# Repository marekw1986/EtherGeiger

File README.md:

# EtherGeiger

## Overview

This is firmware for Ethergeiger project, described on my [Hackaday.io profile](https://hackaday.io/project/163717-ethergeiger-20).

## Required Tools

Project was created in Microchip MPLAB X IDE.
It uses legacy plib.h (https://www.microchip.com/SWLibraryWeb/product.aspx?product=PIC32%20Peripheral%20Library) and MLA libraries (https://www.microchip.com/en-us/tools-resources/develop/libraries/microchip-libraries-for-applications).
You need to use older version of XC32 compiler to build this project (tested with v2.40). Attempt to build it with never version (like 4.xx) leads linker issues.

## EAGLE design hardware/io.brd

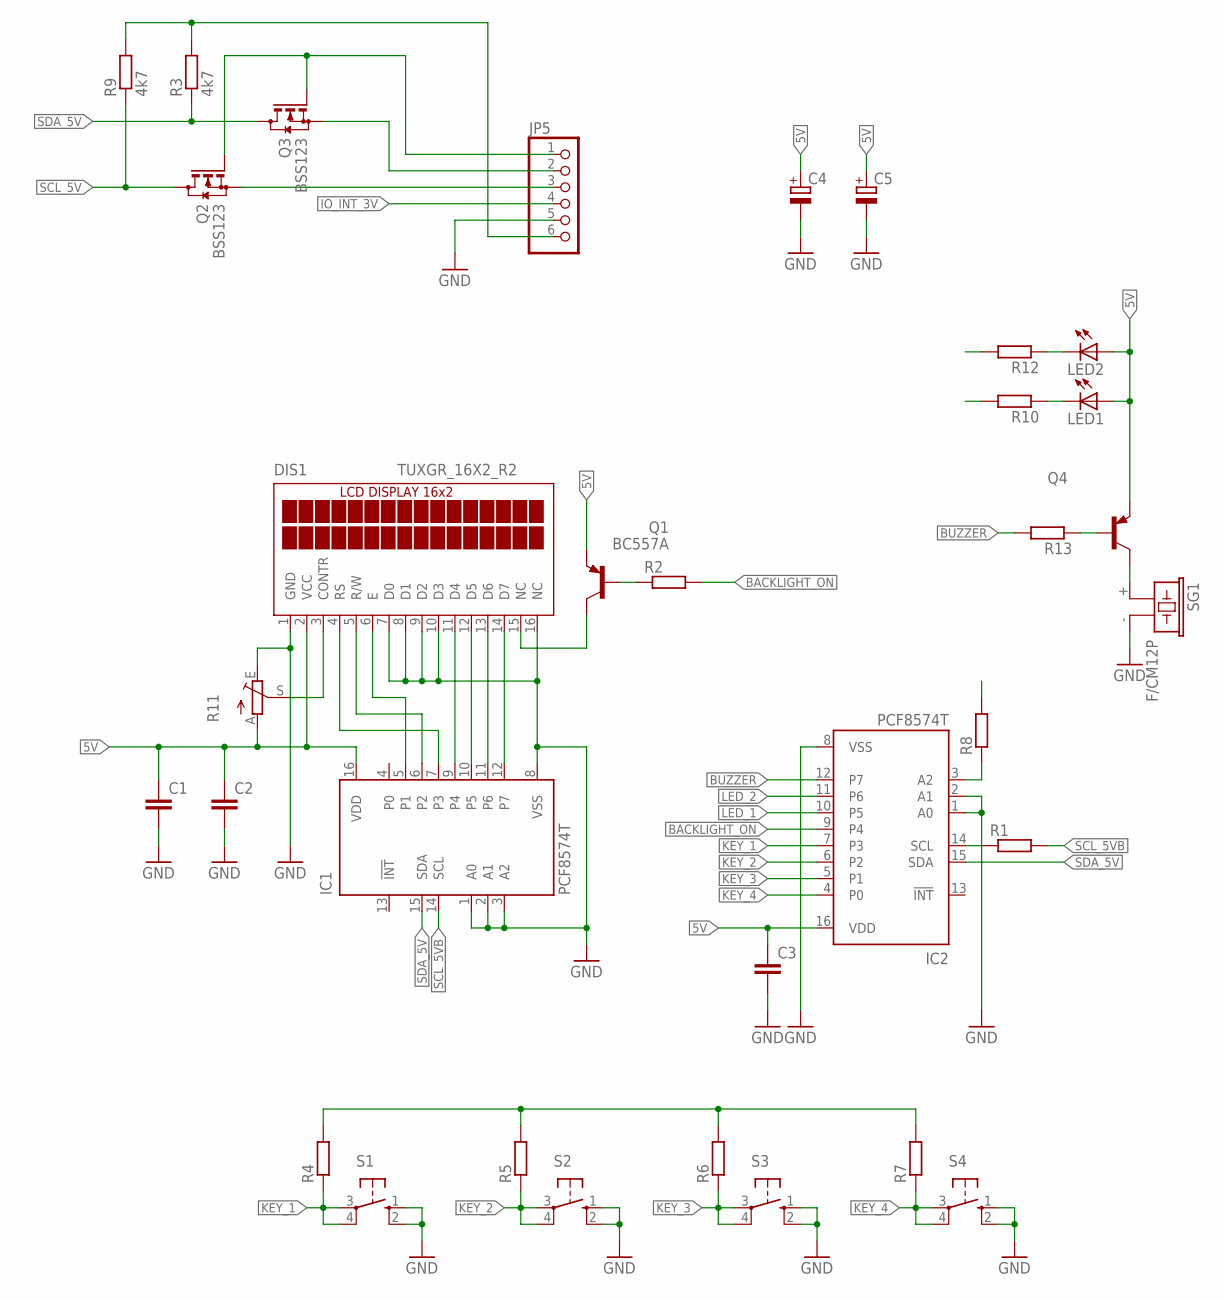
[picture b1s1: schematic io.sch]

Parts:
C1, C3: C-EUC1206; C1206
C2: C-EUC0603; C0603
C4, C5: CPOL-EUSMCD; SMC_D
DIS1: TUXGR_16X2_R2
IC1, IC2: PCF8574T; SO16W
JP5: PINHD-1X6; 1X06
LED1, LED2: LED5MM
Q1: BC557A; TO92-EBC
Q2, Q3: BSS123; SOT23
Q4: BC557A-PNP-TO92-EBC; TO92-EBC
R1, R8, R13: R-EU_R0603; R0603
R2, R6, R7, R10, R12: R-EU_0204/5; 0204/5
R3: 4k7; R0603
R4, R5: R-EU_0204/7; 0204/7
R9: 4k7; R1206
R11: TRIM_EU-B25U; B25U
S1, S2, S3, S4: 10-XX; B3F-10XX
SG1: F/CM12P

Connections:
5V: C1.1, C2.1, C3.1, C4.+, C5.+, DIS1.2 (VCC), IC1.16 (VDD), IC2.16 (VDD), JP5.6, LED1.A, LED2.A, Q1.E, Q4.E, R3.2, R4.2, R5.2, R6.2, R7.2, R8.2, R9.2, R11.A
BACKLIGHT_ON: IC2.9 (P4), R2.2
BUZZER: IC2.12 (P7), R13.2
GND: C1.2, C2.2, C3.2, C4.-, C5.-, DIS1.1 (GND), DIS1.7 (D0), DIS1.8 (D1), DIS1.9 (D2), DIS1.10 (D3), DIS1.16 (NC), IC1.1 (A0), IC1.2 (A1), IC1.3 (A2), IC1.8 (VSS), IC2.1 (A0), IC2.2 (A1), IC2.8 (VSS), JP5.5, R11.E, S1.1 (S), S1.2 (S1), S2.1 (S), S2.2 (S1), S3.1 (S), S3.2 (S1), S4.1 (S), S4.2 (S1), SG1.- (2)
IO_INT_3V: JP5.4
KEY_1: IC2.7 (P3), R4.1, S1.3, S1.4 (P1)
KEY_2: IC2.6 (P2), R5.1, S2.3, S2.4 (P1)
KEY_3: IC2.5 (P1), R6.1, S3.3, S3.4 (P1)
KEY_4: IC2.4 (P0), R7.1, S4.3, S4.4 (P1)
LED_1: IC2.10 (P5), R10.2
LED_2: IC2.11 (P6), R12.2
unnamed: DIS1.14 (D7), IC1.12 (P7)
unnamed: DIS1.13 (D6), IC1.11 (P6)
unnamed: DIS1.12 (D5), IC1.10 (P5)
unnamed: DIS1.11 (D4), IC1.9 (P4)
unnamed: DIS1.6 (E), IC1.5 (P1)
unnamed: DIS1.5 (R/W), IC1.6 (P2)
unnamed: DIS1.4 (RS), IC1.7 (P3)
unnamed: IC2.3 (A2), R8.1
unnamed: DIS1.15 (NC), Q1.C
unnamed: Q1.B, R2.1
unnamed: DIS1.3 (CONTR), R11.S
unnamed: LED1.K (C), R10.1
unnamed: LED2.K (C), R12.1
unnamed: Q4.C, SG1.+ (1)
unnamed: Q4.B, R13.1
SCL_3V: JP5.3, Q2.2 (S)
SCL_5V: IC2.14 (SCL), Q2.3 (D), R1.1, R9.1
SCL_5VB: IC1.14 (SCL), R1.2
SDA_3V: JP5.2, Q3.2 (S)
SDA_5V: IC1.15 (SDA), IC2.15 (SDA), Q3.3 (D), R3.1
_3V: JP5.1, Q2.1 (G), Q3.1 (G)

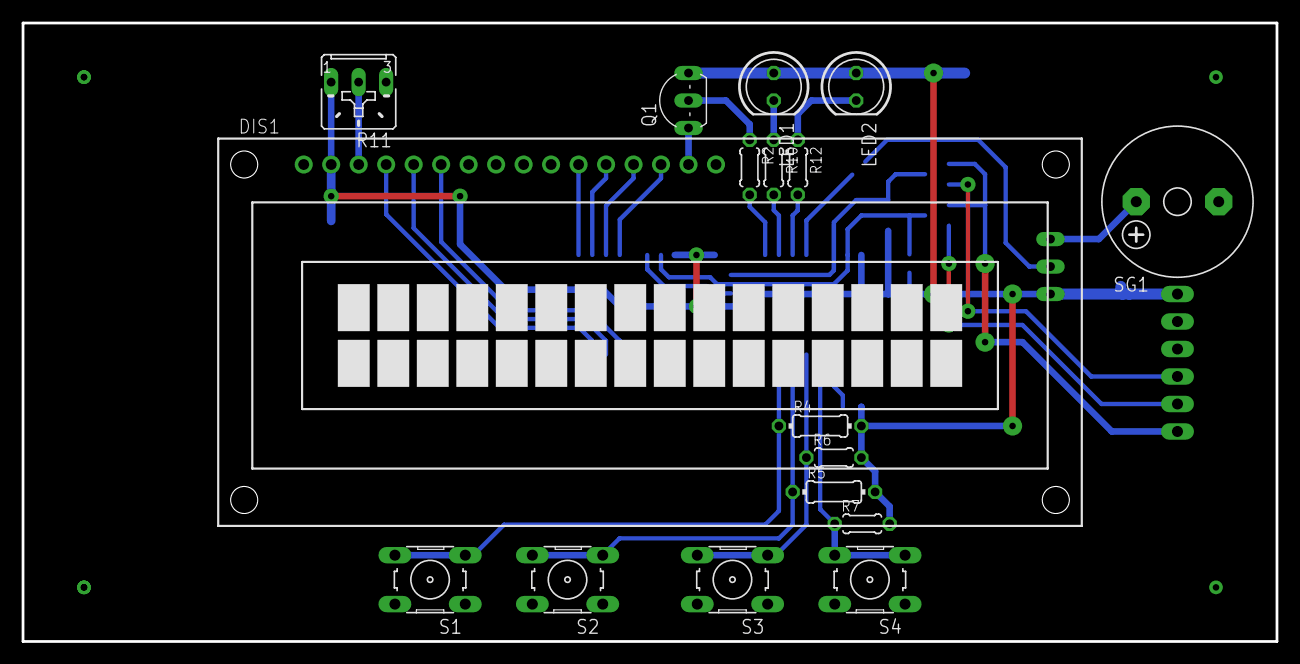
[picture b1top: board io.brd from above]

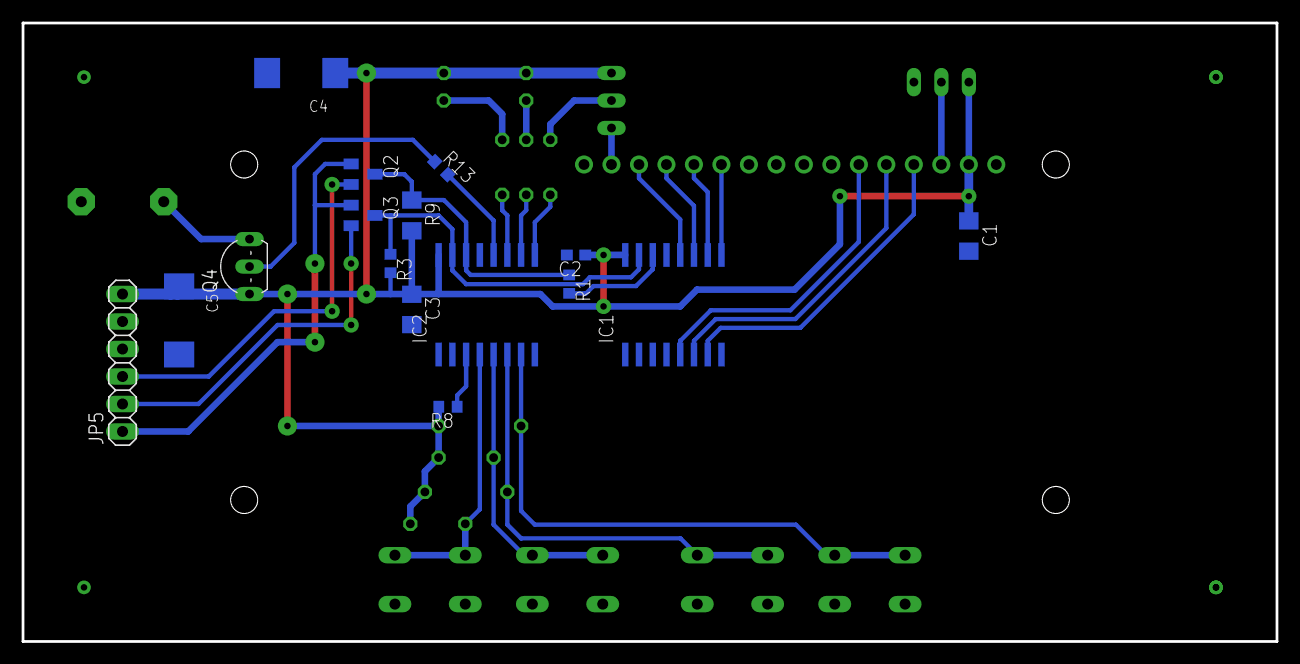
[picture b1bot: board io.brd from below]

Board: 2 copper layers, 115.9 x 57.1 mm, 33 parts (16 on the bottom side), 31 nets.

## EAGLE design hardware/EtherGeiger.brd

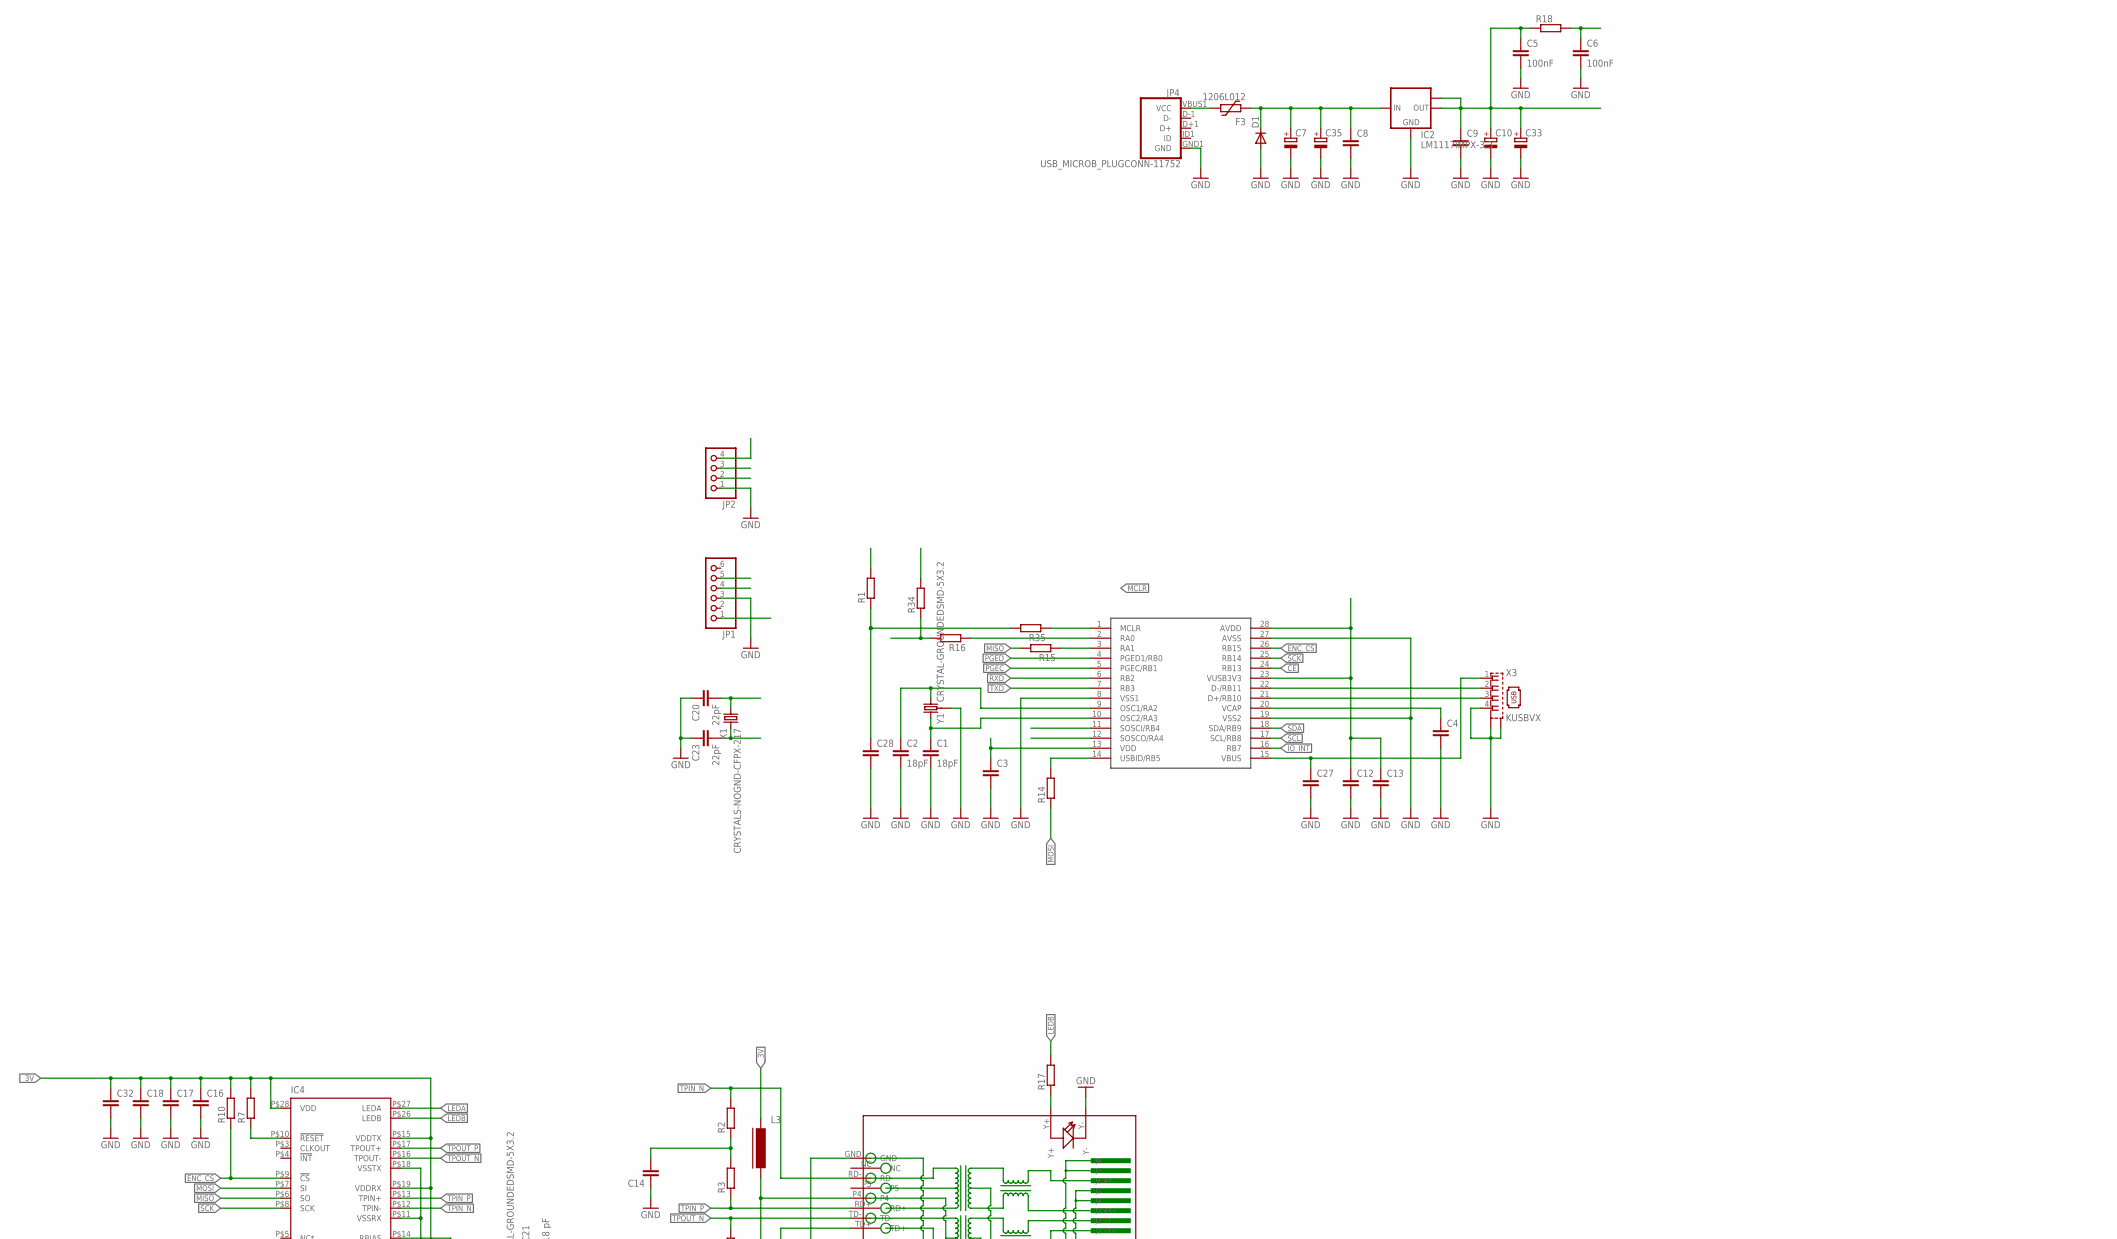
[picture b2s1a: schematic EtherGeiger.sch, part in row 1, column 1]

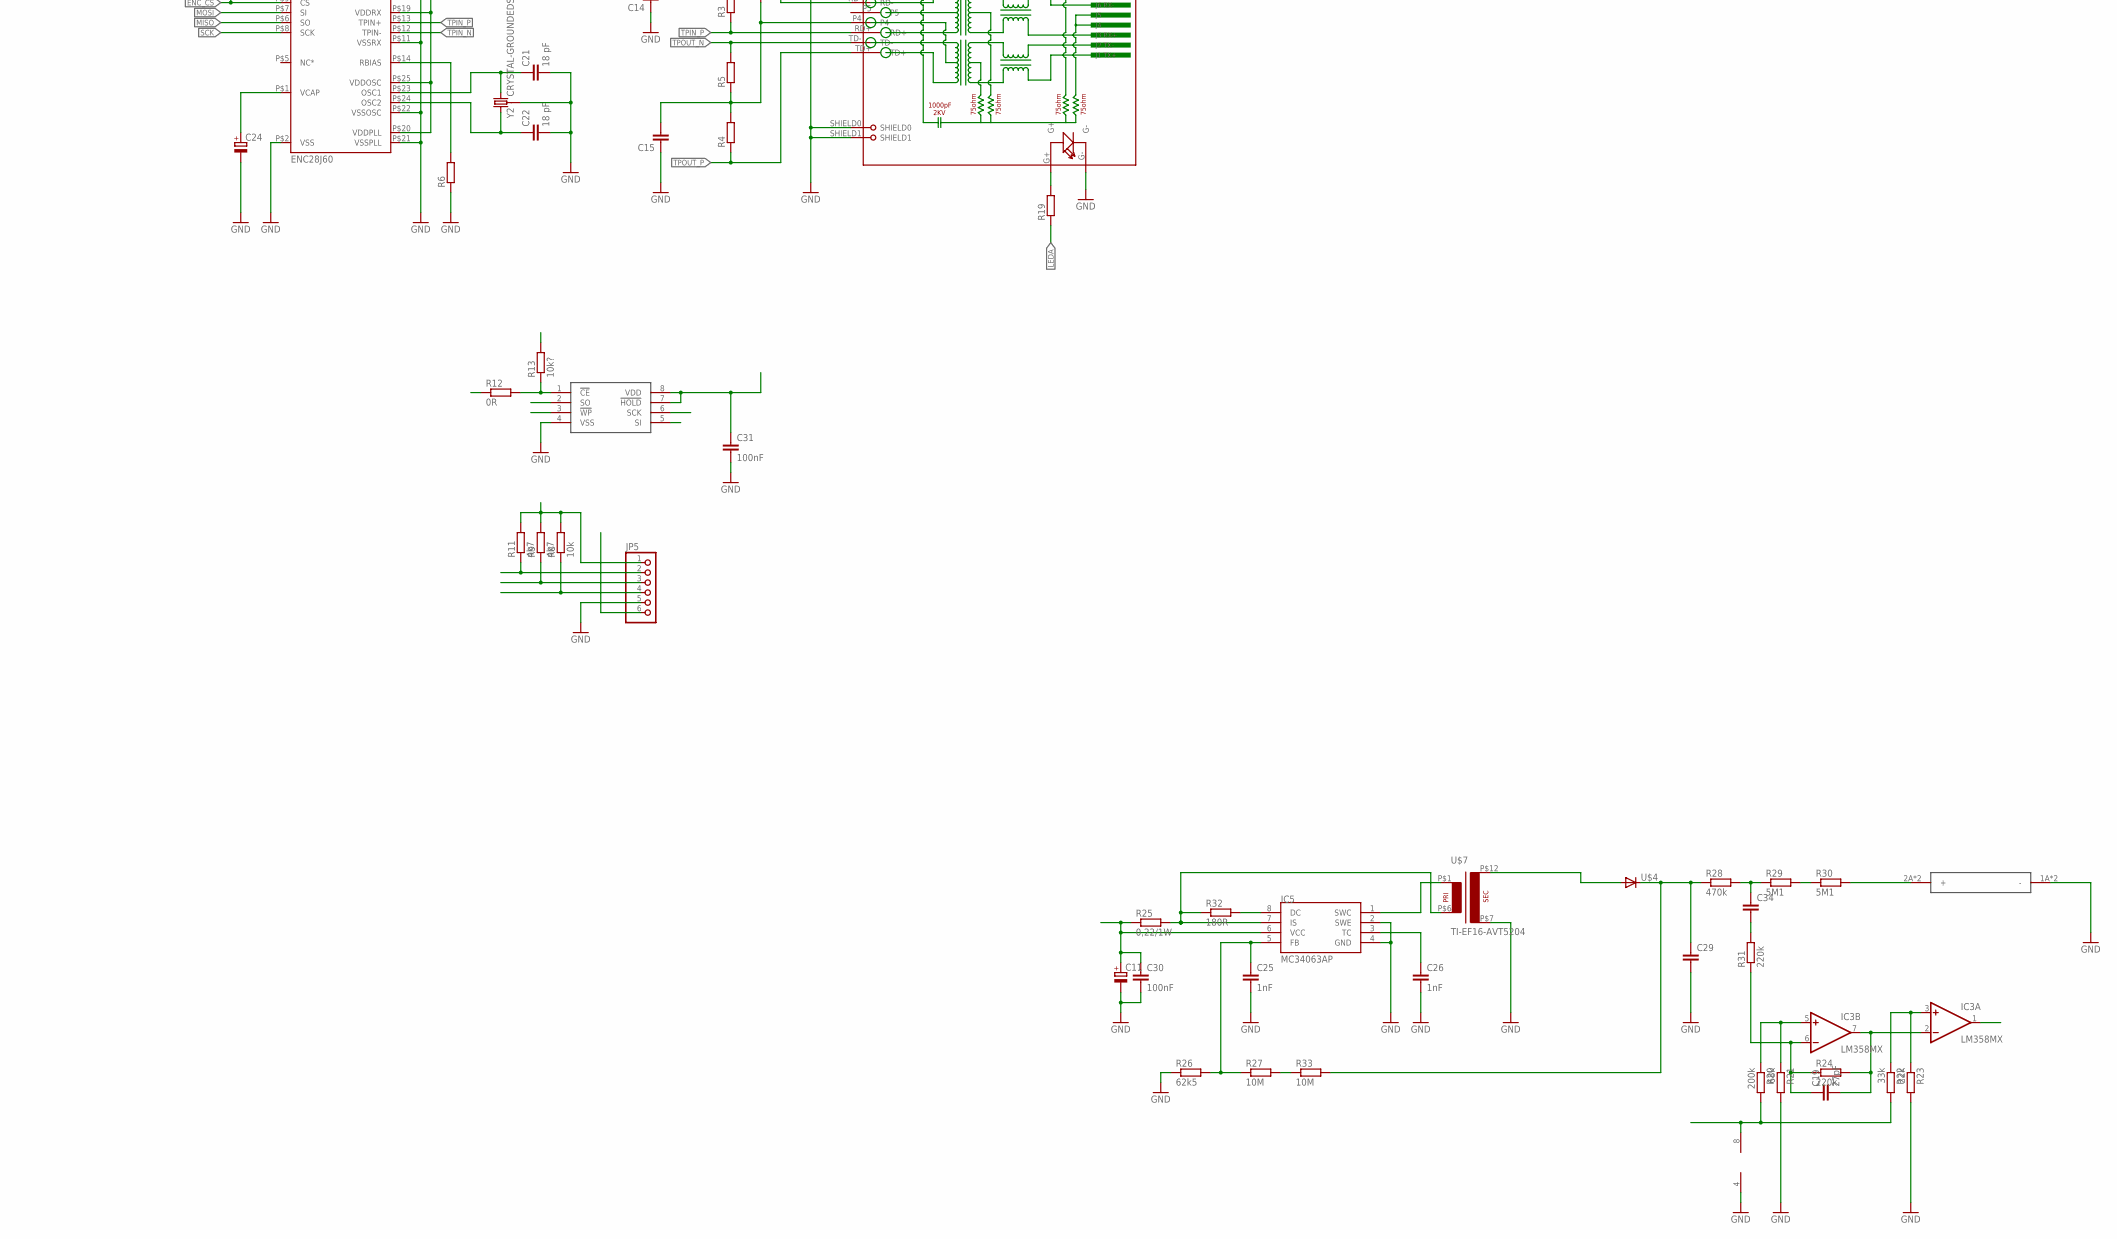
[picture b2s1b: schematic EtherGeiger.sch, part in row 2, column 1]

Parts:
C1, C2: 18pF; C0603
C3, C12, C16, C32: C-EUC0402; C0402
C4, C8, C9, C13, C14, C15, C17, C18, C27, C28: C-EUC0603; C0603
C5, C6, C30, C31: 100nF; C0603
C7: CPOL-EUSMCC; SMC_C
C10: CPOL-EUSMCB; SMC_B
C11: CPOL-EUSMCE; SMC_E
C19: 27pF; C0603
C20, C23: 22pF; C0603
C21, C22: 18 pF; C0603
C24, C33, C35: CPOL-EUSMCA; SMC_A
C25, C26: 1nF; C0603
C29: C-EU225-113X268; C225-113X268
C34: C-EU050-024X044; C050-024X044
D1: DIODE-SMB; SMB
F3: 1206L012; 1206L
IC2: LM1117IMPX-3.3; SOT223
IC3: LM358MX; SO08
IC4: ENC28J60; TSSOP28W
IC5: MC34063AP; DIL08
JP1, JP5: PINHD-1X6; 1X06
JP2: PINHD-1X4; 1X04
JP4: USB_MICROB_PLUGCONN-11752; USB-B-MICRO-SMD_V03
L3: FERRITE-0805; FB805
R1, R2, R3, R4, R5, R7, R10, R14, R15, R34, R35: R-EU_R0603; R0603
R6: R-EU_R0805; R0805
R8: 10k; R0402
R9, R11: 4k7; R0402
R12: 0R; R0603
R13: 10k?; R0603
R16, R17, R18, R19: R-EU_R1206; R1206
R20: 200k; R0603
R21: 68k; R0603
R22: 33k; R0603
R23: 22k; R0603
R24: 220k; R0603
R25: 0,22/1W; R2010
R26: 62k5; R1206
R27, R33: 10M; R2512
R28: 470k; R2512
R29, R30: 5M1; R2512
R31: 220k; M1206
R32: 180R; R0805
RJ1: HR911105A
U$1: PIC32MX250F128B2; SSOP28
U$2: SST25VF016BSO8M; SO-08M
U$4: DIODE-MELF-MLL41; MELF-MLL41
U$5: STS5; GEIGERTUBE
U$7: TI-EF16-AVT5204; EF16-K-H-12P-12,5
X1: CRYSTALS-NOGND-CFPX-217; 3.2X1.5-2-PAD
X3: KUSBVX
Y1, Y2: CRYSTAL-GROUNDEDSMD-5X3.2; CRYSTAL-SMD-5X3.2-4PAD

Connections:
A_3V: C6.1, IC3.8 (V+), R18.2, R20.2, R22.2
CE: R12.1, U$1.24 (RB13)
CE1: R12.2, R13.1, U$2.1 (!CE)
CPM: IC3.1 (OUT), R16.2, R34.1
D_N: U$1.22 (D-/RB11), X3.2
D_P: U$1.21 (D+/RB10), X3.3
ENC_CS: IC4.P$9 (!CS), R10.1, U$1.26 (RB15)
ENC_RST: IC4.P$10 (!RESET), R7.1
GND: C1.2, C2.2, C3.2, C4.2, C5.2, C6.2, C7.-, C8.2, C9.2, C10.-, C11.-, C12.2, C13.2, C14.1, C15.1, C16.2, C17.2, C18.2, C20.1, C21.2, C22.2, C23.1, C24.-, C25.2, C26.2, C27.2, C28.2, C29.2, C30.2, C31.2, C32.2, C33.-, C35.-, D1.A, IC2.1 (GND), IC3.4 (V-), IC4.P$2 (VSS), IC4.P$11 (VSSRX), IC4.P$18 (VSSTX), IC4.P$21 (VSSPLL), IC4.P$22 (VSSOSC), IC5.2 (SWE), IC5.4 (GND), JP1.3, JP2.1, JP4.GND1 (GND), JP5.5, R6.1, R21.2, R23.2, R26.1, RJ1.G-, RJ1.GND, RJ1.SHIELD0, RJ1.SHIELD1, RJ1.Y-, U$1.8 (VSS1), U$1.19 (VSS2), U$1.27 (AVSS), U$2.4 (VSS), U$5.1A (-), U$5.1B (-), U$7.P$7 (P7), X3.4, X3.M1 (S1), X3.M2 (S2), Y1.2 (3), Y1.4 (3), Y2.2 (3), Y2.4 (3)
HV: C29.1, R28.1, R33.2, U$4.C
IO_INT: JP5.4, R8.1, U$1.16 (RB7)
LEDA: IC4.P$27 (LEDA), R19.1
LEDB: IC4.P$26 (LEDB), R17.2
MCLR: JP1.1, R35.1, U$1.1 (MCLR)
MISO: IC4.P$6 (SO), R15.2, U$2.2 (SO)
MOSI: IC4.P$7 (SI), R14.1, U$2.5 (SI)
unnamed: C14.2, R2.1, R3.2
unnamed: IC5.7 (IS), R25.2, R32.1, U$7.P$6 (P6)
unnamed: C19.1, IC3.6 (-IN), R24.1, R31.1
unnamed: C15.2, L3.2, R4.2, R5.1, RJ1.P4
unnamed: C4.1, U$1.20 (VCAP)
unnamed: C19.2, IC3.2 (-IN), IC3.7 (OUT), R24.2
unnamed: C26.1, IC5.3 (TC)
unnamed: IC4.P$14 (RBIAS), R6.2
unnamed: R14.2, U$1.14 (USBID/RB5)
unnamed: F3.1, JP4.VBUS1 (VCC)
unnamed: R15.1, U$1.3 (RA1)
unnamed: R16.1, U$1.2 (RA0)
unnamed: C1.1, U$1.10 (OSC2/RA3), Y1.3 (1)
unnamed: C2.1, U$1.9 (OSC1/RA2), Y1.1 (2)
unnamed: IC3.5 (+IN), R20.1, R21.1
unnamed: IC3.3 (+IN), R22.1, R23.1
unnamed: U$4.A, U$7.P$12 (P12)
unnamed: C21.1, IC4.P$23 (OSC1), Y2.1 (2)
unnamed: C22.1, IC4.P$24 (OSC2), Y2.3 (1)
unnamed: C25.1, IC5.5 (FB), R26.2, R27.1
unnamed: R30.2, U$5.2A (+), U$5.2B (+)
unnamed: R29.2, R30.1
unnamed: C34.1, R28.2, R29.1
unnamed: C34.2, R31.2
unnamed: C24.+, IC4.P$1 (VCAP)
unnamed: R17.1, RJ1.Y+
unnamed: R19.2, RJ1.G+
unnamed: IC5.1 (SWC), U$7.P$1 (P1)
unnamed: IC5.8 (DC), R32.2
unnamed: R27.2, R33.1
PGEC: JP1.5, U$1.5 (PGEC/RB1)
PGED: JP1.4, U$1.4 (PGED1/RB0)
RXD: JP2.3, U$1.6 (RB2)
SCK: IC4.P$8 (SCK), U$1.25 (RB14), U$2.6 (SCK)
SCL: JP5.3, R9.1, U$1.17 (SCL/RB8)
SDA: JP5.2, R11.1, U$1.18 (SDA/RB9)
SOSCI: C20.2, U$1.11 (SOSCI/RB4), X1.1
SOSCO: C23.2, U$1.12 (SOSCO/RA4), X1.2
TPIN_N: IC4.P$12 (TPIN-), R2.2, RJ1.RD-
TPIN_P: IC4.P$13 (TPIN+), R3.1, RJ1.RD+
TPOUT_N: IC4.P$16 (TPOUT-), R5.2, RJ1.TD-
TPOUT_P: IC4.P$17 (TPOUT+), R4.1, RJ1.TD+
TXD: JP2.2, U$1.7 (RB3)
VBUS: C7.+, C8.1, C11.+, C27.1, C30.1, C35.+, D1.C, F3.2, IC2.3 (IN), IC5.6 (VCC), JP5.6, R25.1, U$1.15 (VBUS), X3.1
_3V: C3.1, C5.1, C9.1, C10.+, C12.1, C13.1, C16.1, C17.1, C18.1, C31.1, C32.1, C33.+, IC2.2 (OUT), IC2.TAB (OUT1), IC4.P$15 (VDDTX), IC4.P$19 (VDDRX), IC4.P$20 (VDDPLL), IC4.P$25 (VDDOSC), IC4.P$28 (VDD), JP2.4, JP5.1, L3.1, R1.2, R7.2, R8.2, R9.2, R10.2, R11.2, R13.2, R18.1, R34.2, U$1.13 (VDD), U$1.23 (VUSB3V3), U$1.28 (AVDD), U$2.3 (!WP), U$2.7 (!HOLD), U$2.8 (VDD)
_MCLR: C28.1, R1.1, R35.2

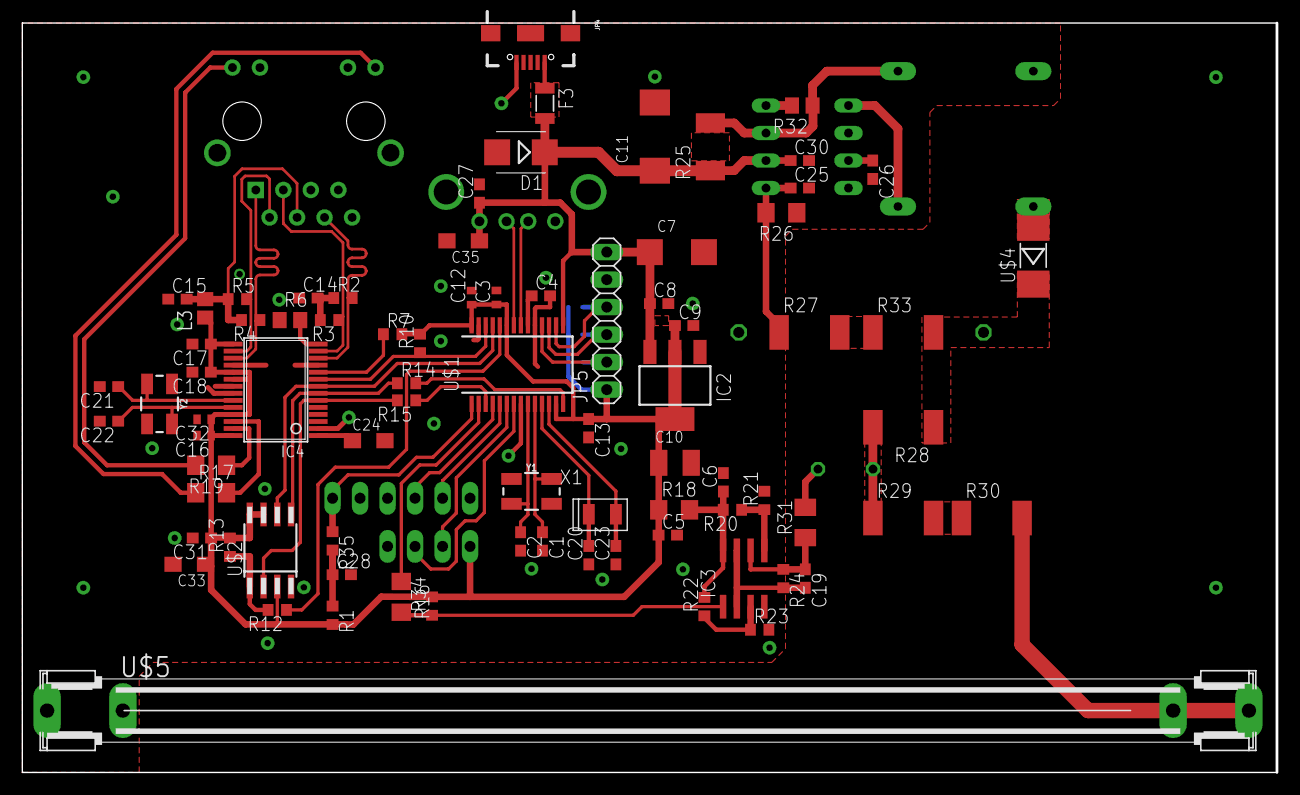
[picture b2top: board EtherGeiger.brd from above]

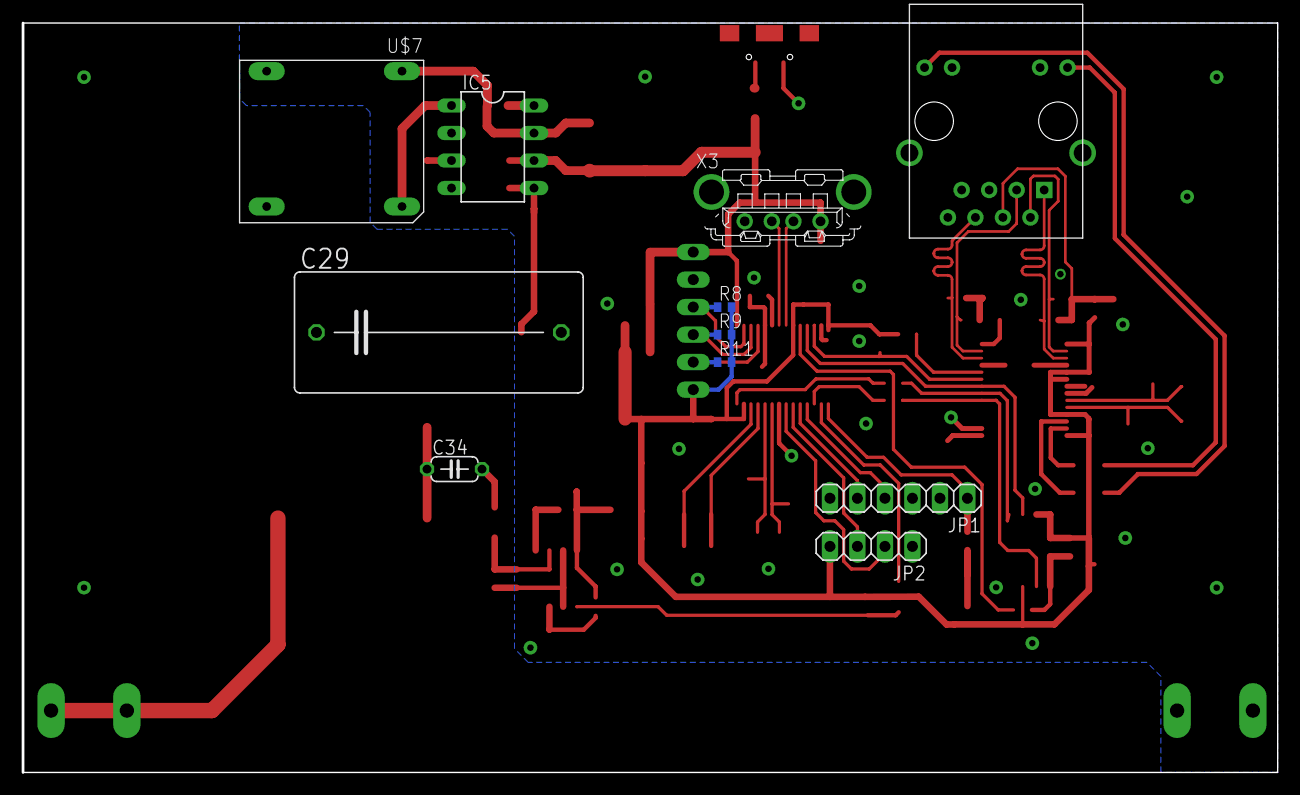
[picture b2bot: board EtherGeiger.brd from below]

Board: 2 copper layers, 115.9 x 69.2 mm, 91 parts (11 on the bottom side), 62 nets.

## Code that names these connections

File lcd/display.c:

#include <time.h>
#include "display.h"
#include "hd44780.h"
#include "../delay/delay.h"
#include "../time/time.h"
#include "../common.h"
#include "../geiger/geiger.h"
#include "../config/config.h"

#define KEY_1 3
#define KEY_2 2
#define KEY_3 1
#define KEY_4 0

disp_state_t disp_state = DISP_MEASUREMENTS;
uint32_t backlight_timer = 0;


static void disp_time_process (uint8_t now);
static void disp_measurements_process (uint8_t now);
static void disp_config_process (uint8_t now);
static void backlight_on (void);

void handle_io (void) {
    uint8_t keys;
    static uint32_t keys_timer = 0; 
    
    switch(disp_state) {
        case DISP_TIME:
        disp_time_process(0);
        break;
        
        case DISP_MEASUREMENTS:
        disp_measurements_process(0);
        break;
        
        case DISP_CONFIG:
        disp_config_process(0);
        break;
        
        default:
        break;
    }
    
    if ( (uint32_t)(millis()-keys_timer) > 50 ) {
        keys = i2c_rcv_byte(PCF8574_IO_ADDR);
        keys_timer = millis();
        if (!(keys & (1 << KEY_1))) {
            backlight_on();
            disp_state = DISP_TIME;
            disp_time_process(1);
        }
        if (!(keys & (1 << KEY_2))) {
            backlight_on();
            disp_state = DISP_MEASUREMENTS;
            disp_measurements_process(1);
        }
        if (!(keys & (1 << KEY_3))) {
            backlight_on();
            disp_state = DISP_CONFIG;
            disp_config_process(1);
        }        
        if (!(keys & (1 << KEY_4))) {
            backlight_on();
        }
        
    }
    
    //turn off backlight automatically
    if (backlight_timer && ((uint32_t)(millis()-backlight_timer) > 5000 ) ) {
        i2c_send_byte(0xFF, PCF8574_IO_ADDR);
        backlight_timer = 0;
    }    
}

void disp_time_process (uint8_t now) {
    time_t rawtime;
    struct tm * timeinfo;
    static uint32_t timer = 0;
    char buff[32];
    
    if (now || (uint32_t)(millis()-timer) > 1000 ) {
        rawtime = rtccGetTimestamp();
        timeinfo = localtime(&rawtime);
        sprintf(buff, "%02d:%02d:%02d", timeinfo->tm_hour, timeinfo->tm_min, timeinfo->tm_sec);
        lcd_cls();
        lcd_locate(0, 0);
        lcd_str(buff);
        lcd_locate(1,0);
        sprintf(buff, "%02d-%02d-%04d", timeinfo->tm_mday, timeinfo->tm_mon, (timeinfo->tm_year + 1900));
        lcd_str(buff);
        timer = millis();
    }
}

void disp_measurements_process (uint8_t now) {
    typedef enum {DISP_MEAS_RAD, DISP_MEAS_TEMP, DISP_MEAS_HUM, DISP_MEAS_PRESS} disp_mesurements_stage_t;
    static disp_mesurements_stage_t disp_mesurements_stage = DISP_MEAS_RAD;
    static uint32_t timer = 0;
    double siv; 
    char buff[32];
    
    if (now || (uint32_t)(millis()-timer) > 5000 ) {
        lcd_cls();
        lcd_locate(0,0);
        switch(disp_mesurements_stage) {
            case DISP_MEAS_RAD:
            lcd_str("Promieniowanie:");
            lcd_locate(1,0);
            siv = cpm2sievert(cpm());
            sprintf(buff, "%.4f uS/h", siv);
            break;
            
            case DISP_MEAS_TEMP:
            lcd_str("Temperatura:");
            lcd_locate(1,0);
            sprintf(buff, "%.2f st. C", bme_temperature);            
            break;
            
            case DISP_MEAS_HUM:
            lcd_str("Wilgotnosc:");
            lcd_locate(1,0);
            sprintf(buff, "%.2f%%", bme_humidity);             
            break;
            
            case DISP_MEAS_PRESS:
            lcd_str("Cisnienie:");
            lcd_locate(1,0);
            sprintf(buff, "%.2f hPa", bme_pressure);             
            break;
            
            default:
            break;
        }
        lcd_str(buff);
        
        disp_mesurements_stage++;
        if (disp_mesurements_stage > DISP_MEAS_PRESS) disp_mesurements_stage = DISP_MEAS_RAD;        
        timer = millis();
    }    
}

void disp_config_process (uint8_t now) {
    typedef enum {DISP_CONFIG_IP, DISP_CONFIG_NETMASK, DISP_CONFIG_GW, DISP_CONFIG_DNS1, DISP_CONFIG_DNS2} disp_config_stage_t;
    static disp_config_stage_t disp_config_stage = DISP_CONFIG_IP;
    static uint32_t timer = 0;
    char buff[32];
    
    if (now || (uint32_t)(millis()-timer) > 5000 ) {
        lcd_cls();
        lcd_locate(0,0);
        switch(disp_config_stage) {
            case DISP_CONFIG_IP:
            lcd_str("IP:");
            lcd_locate(1,0);
            sprintf(buff, "%d.%d.%d.%d", AppConfig.MyIPAddr.v[0], AppConfig.MyIPAddr.v[1], AppConfig.MyIPAddr.v[2], AppConfig.MyIPAddr.v[3]);
            break;
            
            case DISP_CONFIG_NETMASK:
            lcd_str("Maska podsieci:");
            lcd_locate(1,0);
            sprintf(buff, "%d.%d.%d.%d", AppConfig.MyMask.v[0], AppConfig.MyMask.v[1], AppConfig.MyMask.v[2], AppConfig.MyMask.v[3]);                        
            break;
            
            case DISP_CONFIG_GW:
            lcd_str("Brama domyslna:");
            lcd_locate(1,0);
            sprintf(buff, "%d.%d.%d.%d", AppConfig.MyGateway.v[0], AppConfig.MyGateway.v[1], AppConfig.MyGateway.v[2], AppConfig.MyGateway.v[3]);                        
            break;
            
            case DISP_CONFIG_DNS1:
            lcd_str("DNS1:");
            lcd_locate(1,0);
            sprintf(buff, "%d.%d.%d.%d", AppConfig.PrimaryDNSServer.v[0], AppConfig.PrimaryDNSServer.v[1], AppConfig.PrimaryDNSServer.v[2], AppConfig.PrimaryDNSServer.v[3]);                                                 
            break;
            
            case DISP_CONFIG_DNS2:
            lcd_str("DNS2:");
            lcd_locate(1,0);
            sprintf(buff, "%d.%d.%d.%d", AppConfig.SecondaryDNSServer.v[0], AppConfig.SecondaryDNSServer.v[1], AppConfig.SecondaryDNSServer.v[2], AppConfig.SecondaryDNSServer.v[3]);                         
            break;            
            
            default:
            break;
        }
        lcd_str(buff);        
        disp_config_stage++;
        if (disp_config_stage > DISP_CONFIG_DNS2) disp_config_stage = DISP_CONFIG_IP;
        timer = millis();
    }    
}

void backlight_on (void) {
    i2c_send_byte(0xEF, PCF8574_IO_ADDR);
    backlight_timer = millis();
}

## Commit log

2019-06-05 mqtt added
2020-08-25 some updates
2020-08-27 README.md updated
2020-08-28 minor changes
2020-09-13 Some changes
2020-09-18 PCB added
2021-03-11 UI updates
2021-03-11 Cleaned
2022-05-24 MQTT works now
2022-05-24 MQTT
2022-08-04 HTTP UI and MQTT
2022-08-05 JSON
2022-08-06 fixes
2022-08-07 MQTT fix
2022-08-10 Fixes in MQTT library
2022-08-10 MQTT closes gracefully now
2022-08-10 MQTT disconnect fix
2022-08-10 MsqId fixed
2022-08-11 MQTTReadPacket fixes
2022-08-11 MQTT general cleanup
2022-08-14 MQTT rebased
2022-08-14 Refactoring MQTT library
2022-08-14 MQTT refactoring
2022-08-14 MQTT fixes - incomming messages
2022-08-15 MQTT receiving messages
2022-08-15 MQTT fixes
2022-08-27 MQTT rewritten
2022-08-29 some fixes
2022-10-16 FatFS updated to R0.14b
2022-10-17 Memory friendly SPI Flash IO routines implemented
2022-10-17 RAM usage optimization
2024-01-01 itoa replaced with snprintf, gitignore and README.md updated
2025-10-05 Addid HomeAssistant discovery messages (work in progress)
2025-10-05 Send discover messages only once, when MQTT connection is established for the first time after bootup
2025-10-05 Minor cleanup
2025-10-05 Retained messages fix
2025-10-05 Discovery messages are working
2025-10-05 Discovery messages work
2025-10-05 Pressure added to MQTT reports
2025-10-05 Default config changes, unique ID calculated from MAC, proper units reported in discovery messages
2025-10-05 Minor fix
2025-10-05 Shortened names of fields in discovery message
2025-10-05 Another fix
2025-10-05 Updates suspended after MQTT disconnect
2025-10-06 HomeAssistant MQTT code moved to separate files. Proper FSM introduced.
2025-10-23 Separate timers for each MQTT mesage

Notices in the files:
parts and their libraries:
SparkFun-Connectors: Licensing: Creative Commons ShareAlike 4.0 International - https://creativecommons.org/licenses/by-sa/4.0
